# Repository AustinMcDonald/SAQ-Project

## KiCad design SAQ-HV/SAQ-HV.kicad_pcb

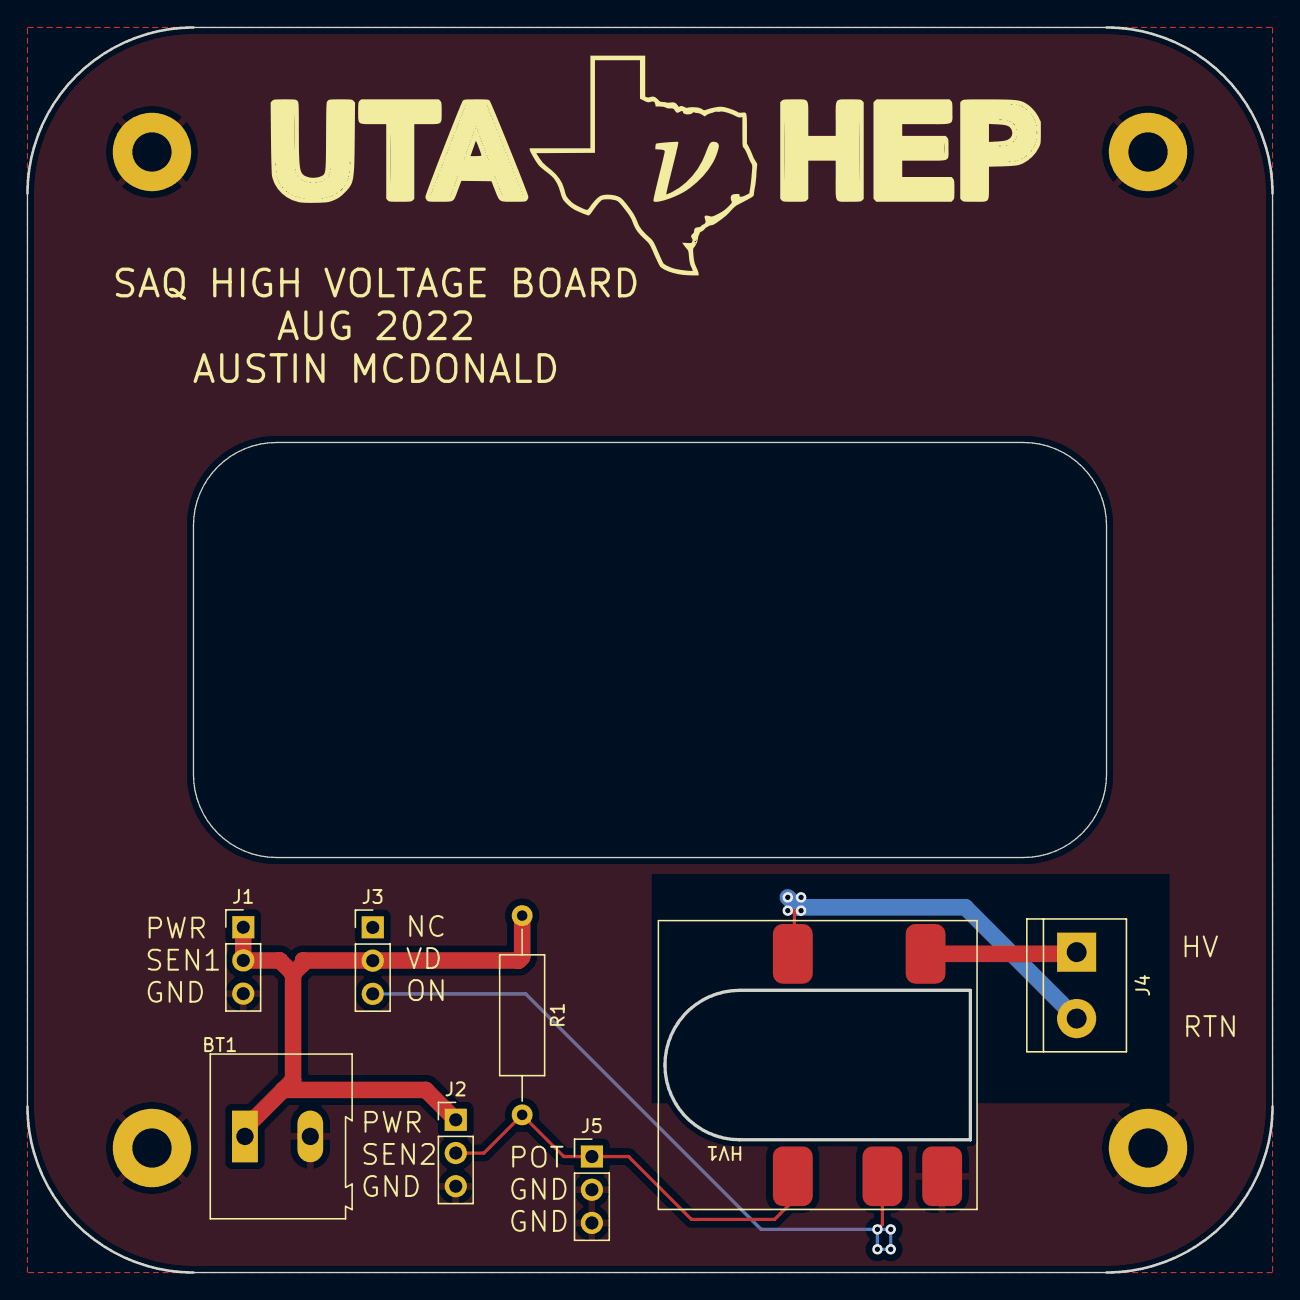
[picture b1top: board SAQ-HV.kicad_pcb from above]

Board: 2 copper layers, 95.2 x 95.2 mm, 12 parts (0 on the bottom side), 6 nets.

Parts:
BT1: 4.5V [3X C]; TerminalBlock_Altech_AK300-2_P5.00mm
H1, H2, H3, H4: MountingHole_Pad; MountingHole_3mm_Pad
HV1: AG10P-5
J1: BAT CHECK; PinHeader_1x03_P2.54mm_Vertical
J2: SET VOLTAGE; PinHeader_1x03_P2.54mm_Vertical
J3: HV-ON\OFF; PinHeader_1x03_P2.54mm_Vertical
J4: Screw_Terminal_01x02; TerminalBlock_bornier-2_P5.08mm
J5: PANNEL-POT; PinHeader_1x03_P2.54mm_Vertical
R1: 2k; R_Axial_DIN0309_L9.0mm_D3.2mm_P15.24mm_Horizontal

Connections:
Meter2 SEN: HV1.5 (CTL), J2.2, J5.1, R1.2
Meter GND: BT1.2 (-), H1.1, H2.1, H3.1, H4.1, HV1.1 (-IN), J1.3, J2.3, J5.2, J5.3
Meter PWR: BT1.1 (+), J1.1, J1.2, J2.1, J3.2, R1.1
unnamed: HV1.2 (+IN), J3.3
unnamed: HV1.3 (HV-OUT), J4.1
unnamed: HV1.4 (HV-RTN), J4.2

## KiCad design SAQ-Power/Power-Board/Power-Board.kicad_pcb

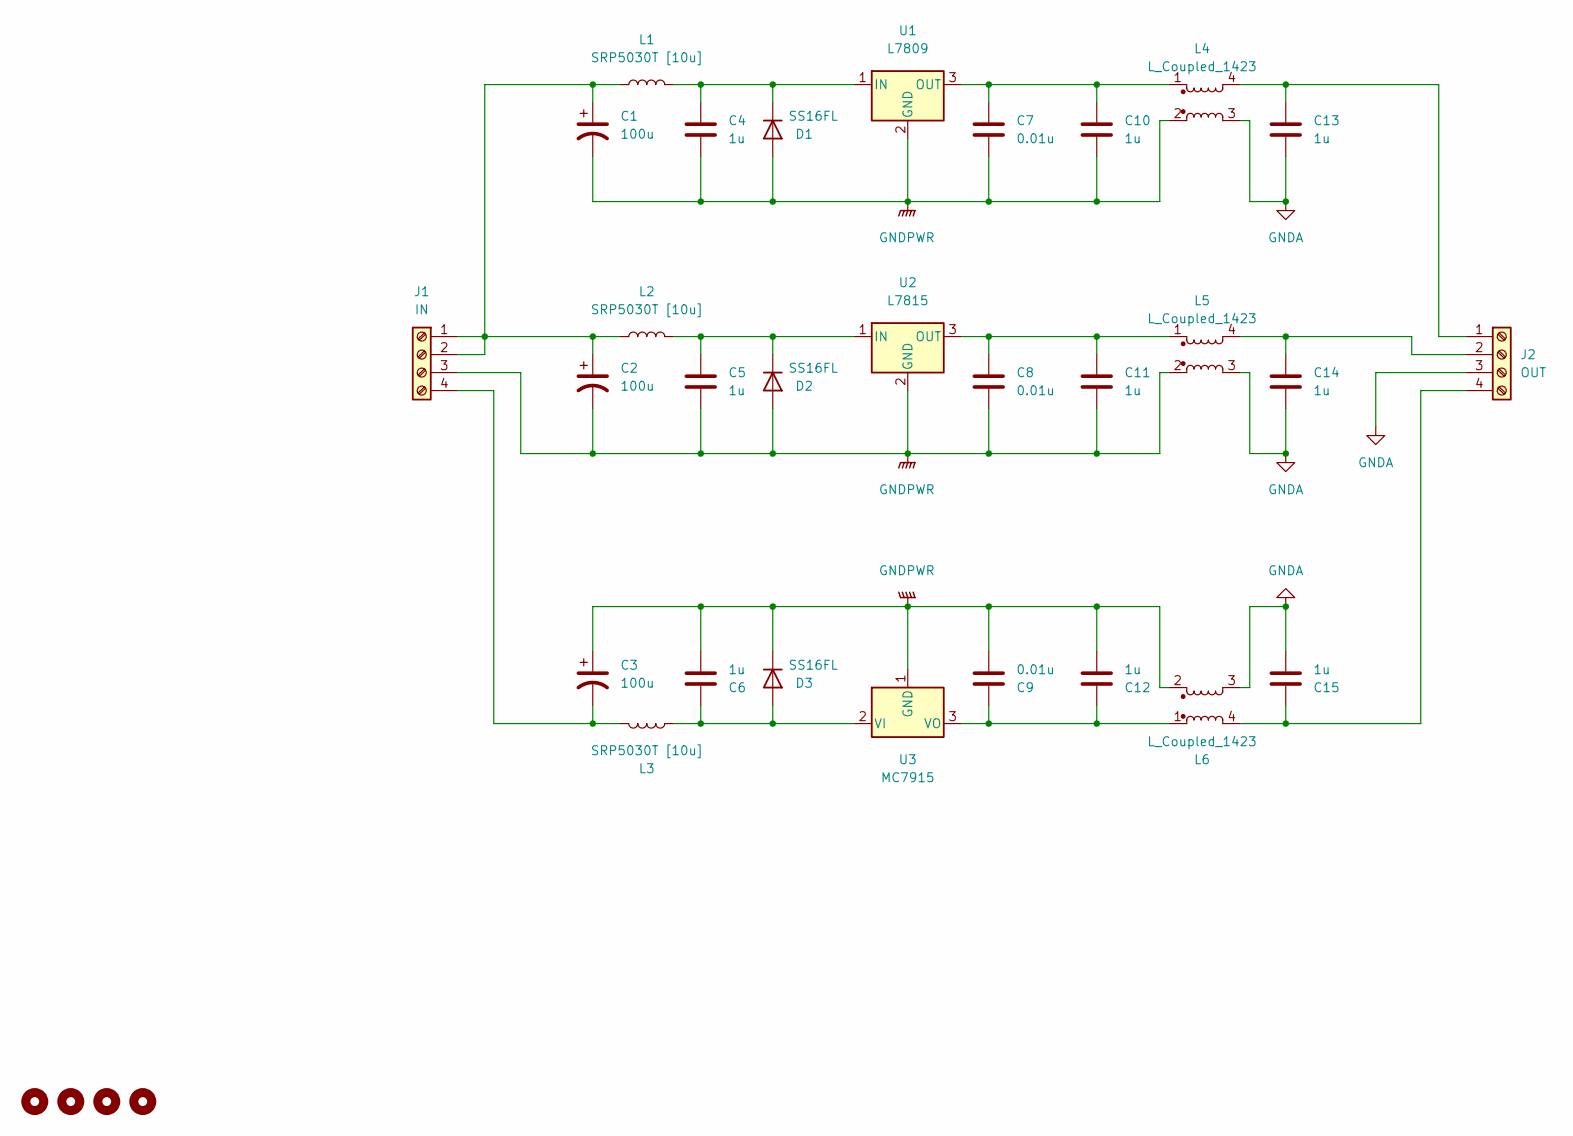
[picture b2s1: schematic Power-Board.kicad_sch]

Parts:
C1, C2, C3: 100u; C_Elec_8x10.2
C4, C5, C6, C10, C11, C12, C13, C14, C15: 1u; C_1206_3216Metric_Pad1.33x1.80mm_HandSolder
C7, C8, C9: 0.01u; C_1206_3216Metric_Pad1.33x1.80mm_HandSolder
D1, D2, D3: SS16FL; D_SMA_Handsoldering
H1, H2, H3, H4: MountingHole; MountingHole_3.2mm_M3
J1: IN; TerminalBlock_bornier-4_P5.08mm
J2: OUT; TerminalBlock_bornier-4_P5.08mm
L1, L2, L3: SRP5030T [10u]; L_Bourns_SRP5030T
L4, L5, L6: L_Coupled_1423; L_CommonMode_Wuerth_WE-SL2
U1: L7809; TO-263-3_TabPin2
U2: L7815; TO-263-3_TabPin2
U3: MC7915; TO-263-3_TabPin2

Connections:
GNDA: C13.2, C14.2, C15.2, J2.3, L4.3, L5.3, L6.3
GNDPWR: C1.2, C2.2, C3.1, C4.2, C5.2, C6.2, C7.2, C8.2, C9.2, C10.2, C11.2, C12.2, D1.2 (A), D2.2 (A), D3.1 (K), J1.3, L4.2, L5.2, L6.2, U1.2 (GND), U2.2 (GND), U3.1 (GND)
unnamed: C1.1, C2.1, J1.1, J1.2, L1.1, L2.1
unnamed: C3.2, J1.4, L3.1
unnamed: C4.1, D1.1 (K), L1.2, U1.1 (IN)
unnamed: C5.1, D2.1 (K), L2.2, U2.1 (IN)
unnamed: C6.1, D3.2 (A), L3.2, U3.2 (VI)
unnamed: C7.1, C10.1, L4.1, U1.3 (OUT)
unnamed: C8.1, C11.1, L5.1, U2.3 (OUT)
unnamed: C9.1, C12.1, L6.1, U3.3 (VO)
unnamed: C13.1, J2.1, L4.4
unnamed: C14.1, J2.2, L5.4
unnamed: C15.1, J2.4, L6.4

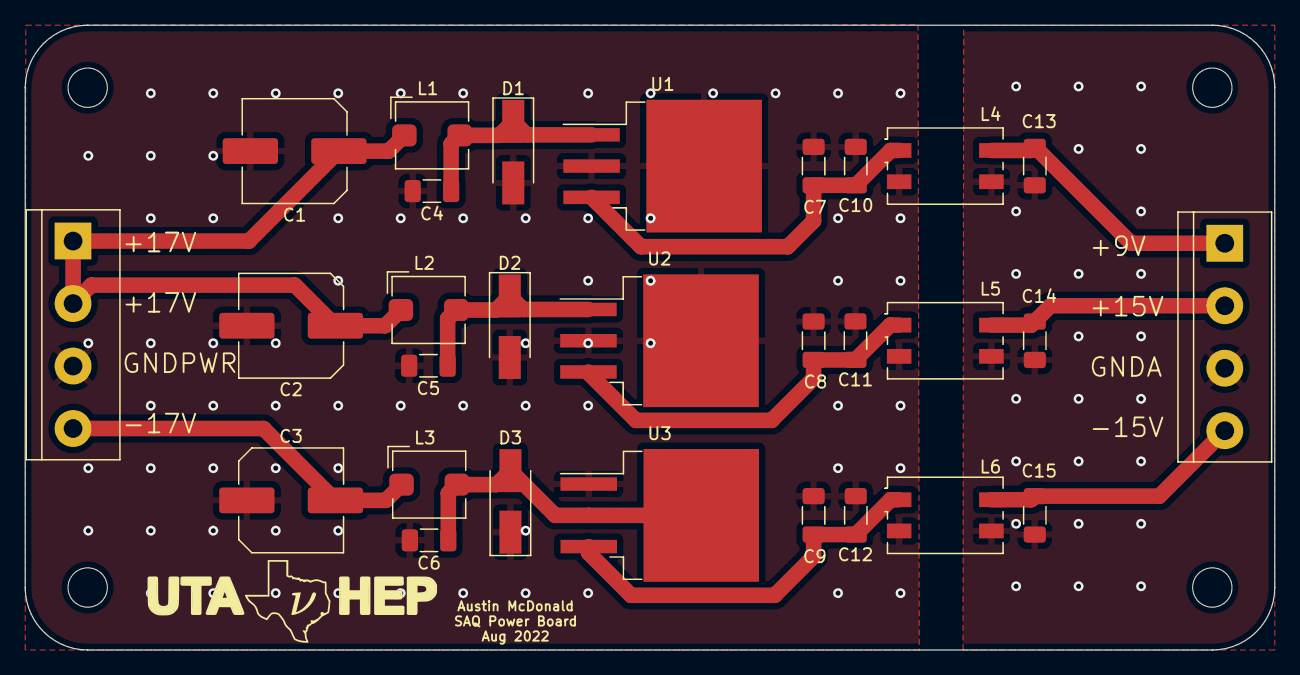
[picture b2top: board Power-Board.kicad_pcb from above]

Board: 2 copper layers, 101.6 x 50.8 mm, 33 parts (0 on the bottom side), 13 nets.

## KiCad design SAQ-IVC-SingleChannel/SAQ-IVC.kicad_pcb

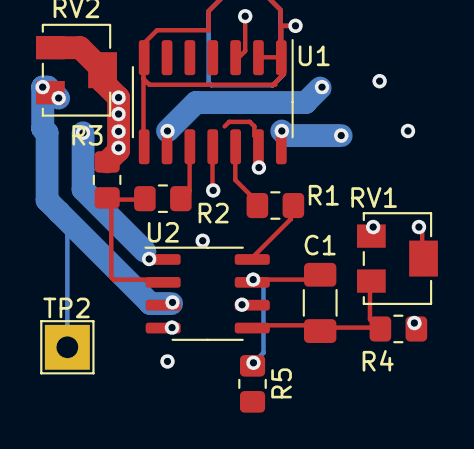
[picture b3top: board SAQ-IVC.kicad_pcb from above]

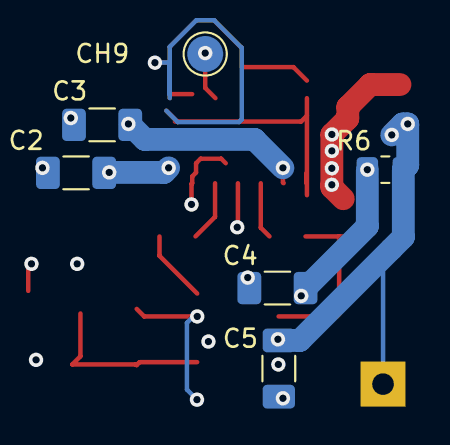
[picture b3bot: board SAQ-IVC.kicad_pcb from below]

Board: 4 copper layers, 17 parts (6 on the bottom side), 12 nets.

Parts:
C1: 10n; C_1206_3216Metric_Pad1.33x1.80mm_HandSolder
C2, C3, C4, C5: 0.1u; C_1206_3216Metric_Pad1.33x1.80mm_HandSolder
CH9: TestPoint_Pad_D2.0mm
R1, R5: 50; R_0805_2012Metric_Pad1.20x1.40mm_HandSolder
R2: 3k; R_0805_2012Metric_Pad1.20x1.40mm_HandSolder
R3, R6: 1k; R_0805_2012Metric_Pad1.20x1.40mm_HandSolder
R4: 2.2k; R_0805_2012Metric_Pad1.20x1.40mm_HandSolder
RV1, RV2: 0->10k; Potentiometer_Bourns_3214W_Vertical
TP2: TestPoint_Alt; TestPoint_THTPad_2.5x2.5mm_Drill1.2mm
U1: IVC102; SOIC-14_3.9x8.7mm_P1.27mm
U2: AD8561; SOIC-8_3.9x4.9mm_P1.27mm

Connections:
+9V: C4.1, R6.2, U2.1 (V+)
+15V: C2.1, U1.14 (+V)
-15V: C3.1, U1.9 (-V)
GND: C2.2, C3.2, C4.2, C5.2, R3.1, RV2.1, RV2.2, U1.1 (int_p), U1.2 (int_n'), U1.7 (nc), U1.8 (GNDA), U2.4 (V-)
GNDD: R4.2, RV1.1, RV1.2, U1.13 (GNDD), U2.6 (GND)
unnamed: C1.1, R4.1, RV1.3, U2.5 (LATCH)
unnamed: C1.2, R5.1, U2.7 (Q)
unnamed: R1.1, U1.12 (S2)
unnamed: R1.2, U2.8 (~Q)
unnamed: R2.1, U1.10 (OUT)
unnamed: R2.2, R3.2, U2.2 (+)
VDD: C5.1, R6.1, RV2.3, TP2.1, U2.3 (-)

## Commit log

2022-09-23 Updated Readout
